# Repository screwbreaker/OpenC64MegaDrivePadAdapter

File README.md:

# OpenC64MegaDrivePadAdapter
OpenC64MegaDrivePadAdapter is an Open Hardware adapter that allows the safe connection of a Sega Mega Drive (known as *Genesis* in the US) controller to a Commodore 64 or Amiga computer.

### Synopsis
This board is a fork of a project of SukkoPera: [github.com/SukkoPera](https://github.com/SukkoPera/), also this document is based on the original version.

The original version of this board can be found here: [github.com/SukkoPera/OpenC64MegaDrivePadAdapter](https://github.com/SukkoPera/OpenC64MegaDrivePadAdapter)

In this version the PCB has a particular shape in order to manage with the Amiga 600 case.
A manual cut of the DB9 connector still required in order to allow this adapter to fit into the A600 port 2. If you are not confident with cut tools, don't do it! A simple extension cable is a perfect and easy solution for this problem. 

This version use switches instead jumpers, this make the configuration much easier, plus now is impossible to set an improper configuration.
Is still recommended to turn off the computer before change the configuration.
The UP direction on the D-PAD is always active, it cannot be disabled. It can be used together with another button configured as UP. An extra diode (D6) is used to separate the two UP lines.

In the older versions of the adapter, sometimes the second button was not recognized by some games, now a transistor is used to fix this issue.
This version is also compatible with the [OpenAmigaJoyMouseSwitcher](https://github.com/SukkoPera/OpenAmigaJoyMouseSwitcher).

Rev 6 also include the mod to allow the amiga to use all the MD pad buttons. Unfortunately at the moment there are no known games or program that can do this. Thanks to SukkoPera for this improvement.

### Summary
Despite being compatible at the physical level (i.e.: they use the same DB-9 connectors), Sega Mega Drive controllers are slightly different from the *Atari-style joysticks* (which the C64 uses) at the electrical level. These differences usually manifest themselves in the fact that certain keyboard keys are not responsive when a Sega Mega Drive pad is connected to a C64 computer, but the CIA chip may also get harmed as a result.

Since I think that the Sega Mega Drive controller is one of the best joypads which ever saw the light, I developed this simple adapter board, which is supposed to sit inbetween the computer and the controller. You should be able to keep it plugged into the computer and then connect the controller to it, but you can also use a joystick extension cord (widely available), if that makes it easier.

Button B will work as the normal fire button, but this adapter also allows using Button C as the second fire button, for those games that support two buttons.

While this all works out of the box on Amiga computers, this adapter also allows to customize the button mapping to a certain degree: for instance, replacing UP with C might make some games more comfortable to play. This might be useful on the Amiga as well, so the adapter also supports an Amiga mode.

In this version the D-PAD UP is always active, it ca be used in games as usual, this is andy for games witch use UP for multiple things: menu, jump, go upstairs, etc.

### Configuration
The board is based on the circuit that was originally published in [issue #5 of Commodore world](https://www.scribd.com/document/8945979/Commodore-World-Issue-05) back in 1994, with a few improvements that will allow an easier gameplay with certain titles.

First of all, be sure to move the C64/Amiga switch to the proper position, before connecting the adapter.

Since most joysticks back in the day only had a single fire button, it was usually used for *firing*, whatever that meant. *Jumping* was usually done with the UP direction of the joystick, which is quite annoying on a joypad.
This is why OpenC64MegaDrivePadAdapter allows you to repurpose the B or C key to jumping, leaving the other button for firing, all at your choice.
It also allows to use C as the second fire button, which is only supported by a few titles. You can even swap B and C, if you prefer.

The switches configurations are showed on a little table printed on the board. F1 and F2 on the table refers to FIRE1 and FIRE2 switches.

The FIRE1 switch select which button to use as FIRE 1, B or C.

The FIRE2 switch select which action the FIRE 2 button must perform, UP (the same of the D-PAD UP) or FIRE.

**ALWAYS TURN YOUR COMPUTER OFF BEFORE MOVING THE CONFIGURATION SWITCHES.**
If you don't follow this rule, **you will probably cause permanent damage to your computer and/or controller**, so **please be careful**, you have been warned.

### Compatibility
This adapter is compatible with every MD gamepad, even the 6 buttons one. And also with the Master System gamepad.

The Mega Drive gamepad is designed to be back compatible with the Master System. B and C on the Mega Drive are BUTTON 1 and BUTTON 2 on the Master System.

To add more buttons on the Mega Drive, SEGA added an extra line (SELECT) wich is toggled HIGH or LOW. The state of this line determinate wich set of buttons the pad must return (B and C or A and START).
Since in this adapter the SELECT line is always HIGH, only the B and C buttons are used.

### License
OpenC64MegaDrivePadAdapter is Open Hardware. If you make any modifications to the board, please contribute them back.

### Support the Project
Since the project is open you are free to get the PCBs made by your preferred manufacturer, however in case you want to support the development, you can order them from PCBWay:

You get cheap, professionally-made and good quality PCBs, the autor of the board get some credit that will help with this and [other projects](https://www.pcbway.com/project/member/?bmbno=W123483A). You won't even have to worry about the various PCB options, it's all pre-configured for you!

Also, if you still have to register to that site, [you can use this link](https://www.pcbway.com/setinvite.aspx?inviteid=41100) to get some bonus initial credit (and some more to the author).

Again, if you want to use another manufacturer, feel free to, don't feel obligated :).

### Get Support
If you need help or have questions, you can join [the official Telegram group](https://t.me/joinchat/HUHdWBC9J9JnYIrvTYfZmg).

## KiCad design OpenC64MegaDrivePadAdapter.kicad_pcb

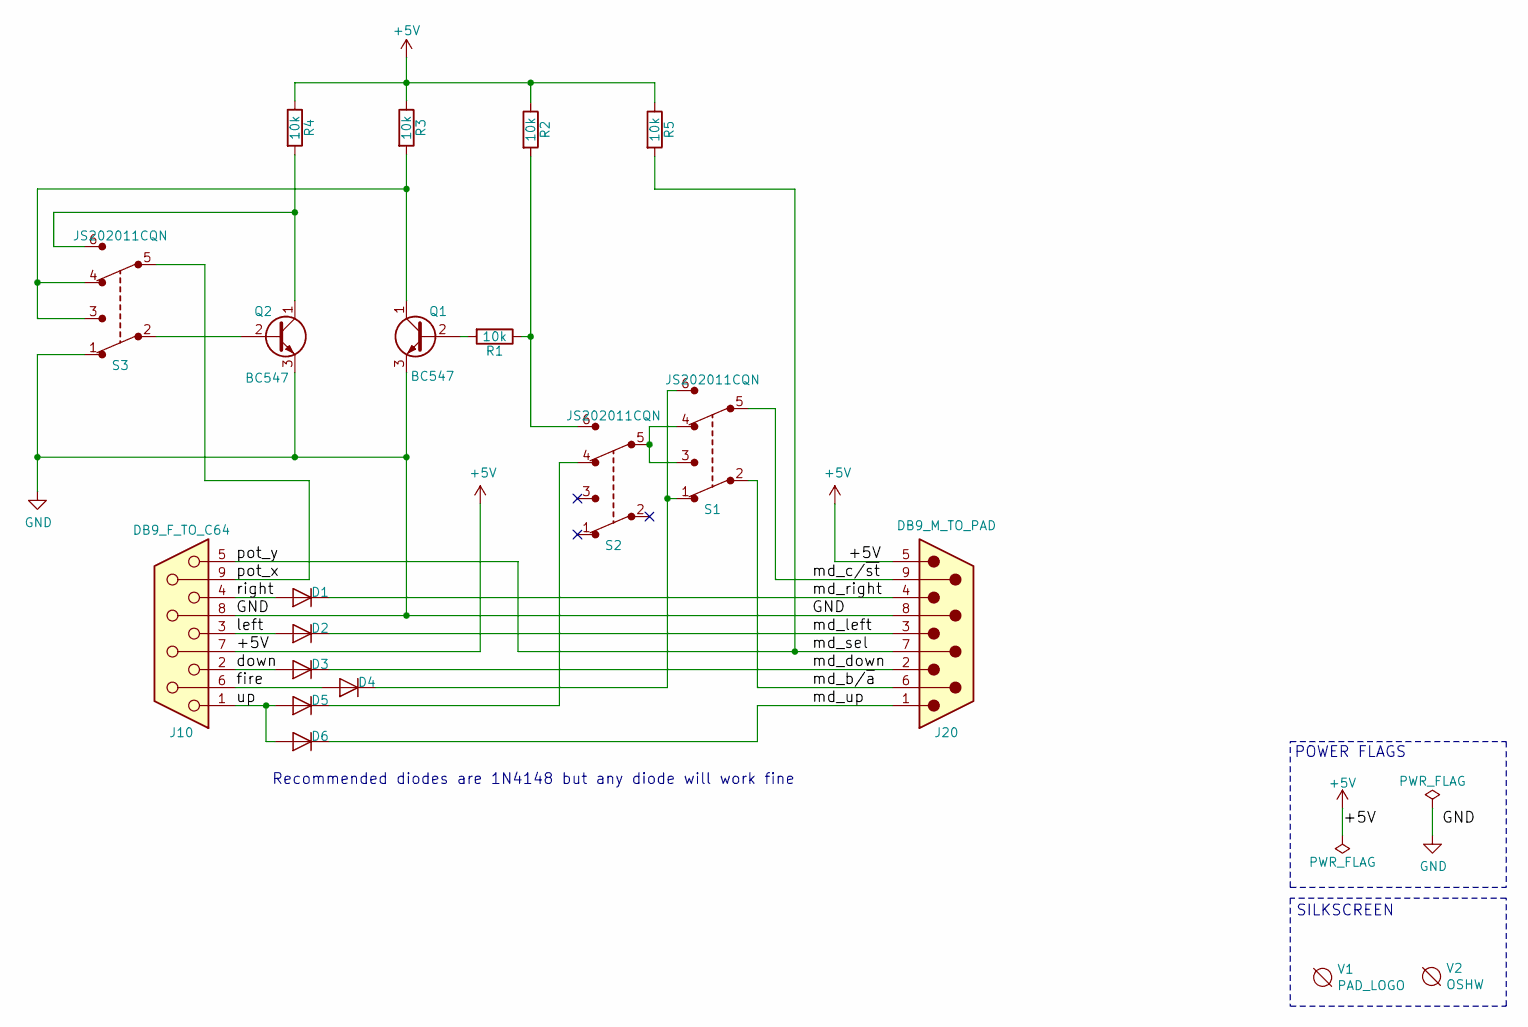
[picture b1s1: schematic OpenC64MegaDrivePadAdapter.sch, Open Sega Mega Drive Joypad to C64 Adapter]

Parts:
D1, D2, D3, D4, D5, D6: 1N4148; D_DO-35_SOD27_P7.62mm_Horizontal
J10: DB9_F_TO_C64; DB_9F
J20: DB9_M_TO_PAD; DB_9M
Q1, Q2: BC547; TO-92L_HandSolder
R1, R2, R3, R4, R5: 10k; R_Axial_DIN0204_L3.6mm_D1.6mm_P7.62mm_Horizontal
S1, S2, S3: JS202011CQN; SW_CuK_JS202011CQN_DPDT_Straight; MPN JS202011CQN; Digi-Key_PN 401-2001-ND
V1: PAD_LOGO; LOGO
V2: OSHW; oshw

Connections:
+5V: J10.7, J20.5, R2.1, R3.1, R4.1, R5.1
/down: D3.2 (A), J10.2
/fire: D4.2 (A), J10.6
/left: D2.2 (A), J10.3
/md_b/~a: J20.6, S1.2
/md_c/~st: J20.9, S1.5
/md_down: D3.1 (K), J20.2
/md_left: D2.1 (K), J20.3
/md_right: D1.1 (K), J20.4
/md_sel: J10.5, J20.7, R5.2
/md_up: D6.1 (K), J20.1
/pot_x: J10.9, S3.5
/right: D1.2 (A), J10.4
/up: D5.2 (A), D6.2 (A), J10.1
GND: J10.8, J20.8, Q1.3 (E), Q2.3 (E), S3.1
unnamed: D4.1 (K), S1.1, S1.6
unnamed: D5.1 (K), S2.4
unnamed: Q1.1 (C), R3.2, S3.3, S3.4
unnamed: Q1.2 (B), R1.2
unnamed: Q2.1 (C), R4.2, S3.6
unnamed: Q2.2 (B), S3.2
unnamed: R1.1, R2.2, S2.6
unnamed: S1.3, S1.4, S2.5

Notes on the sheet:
Recommended diodes are 1N4148 but any diode will work fine
SILKSCREEN
POWER FLAGS

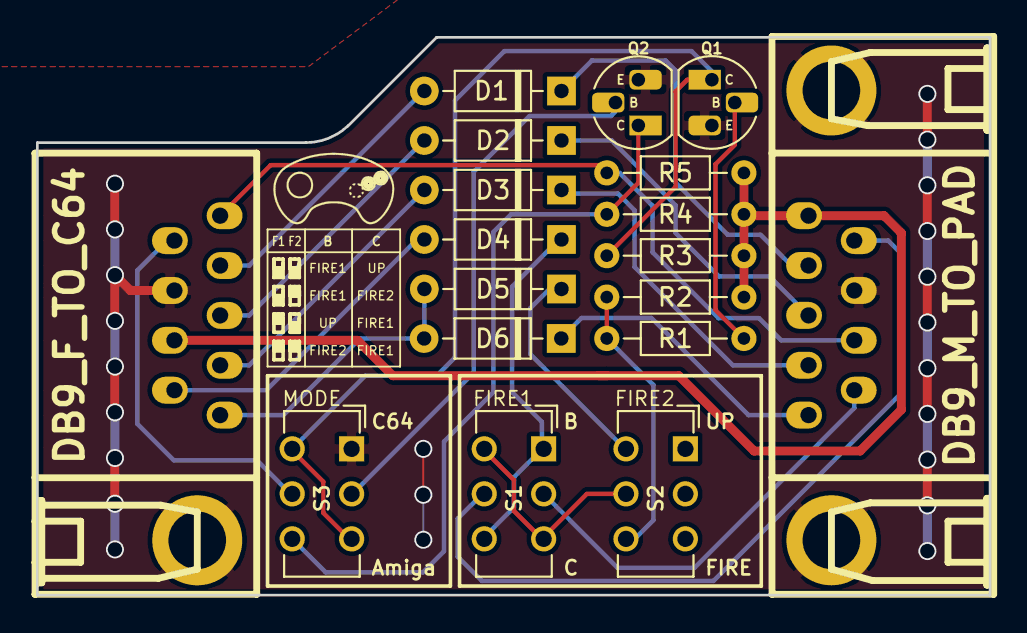
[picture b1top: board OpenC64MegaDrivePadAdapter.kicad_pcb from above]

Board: 2 copper layers, 52.9 x 31.0 mm, 20 parts (1 on the bottom side), 23 nets.

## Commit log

2018-12-31 Align connectors to board edge, move button 2 to pin 9
2018-12-31 V4 renders and schematics
2018-12-31 New README.md
2018-12-31 Not needed in this version
2018-12-31 A different OSHW logo is used in this version
2018-12-31 Empty file just to keep the folder
2018-12-31 OSHW logo
    The EEVBlog variant of the OSHW logo: https://www.eevblog.com/oshw/
2018-12-31 MD pad logo
2018-12-31 DB9 connector
2018-12-31 Simbols library
2018-12-31 Align connectors to board edge
    Align connectors to board edge, move button 2 to pin 9
2018-12-31 V4 schematics
2018-12-31 Main project file
2018-12-31 Netlist
2018-12-31 V4 PCB
2018-12-31 Project custom library
2018-12-31 V4 top render
2018-12-31 3D models
2019-01-01 Interactive BOM
2019-01-09 Bill of Materials
2019-01-09 Added voids elements for silk screen
2019-01-09 Void element for silk screen
    This is a void element to keep on the footprints with only the silk screen on the PCB
2019-01-09 Added voids elements for the silk screen
2019-01-09 Minor changes
2019-04-01 Delete OpenA1200RTC.csv
    wrong project
2019-04-01 rev. 5 renders and schematics
2019-04-01 rev. 5 PCB
2019-04-01 rev. 5 schematics
2019-04-01 empty file
2019-04-01 gerbers
2020-11-12 rev. 6 renders and schematics
2020-11-12 rev 6
